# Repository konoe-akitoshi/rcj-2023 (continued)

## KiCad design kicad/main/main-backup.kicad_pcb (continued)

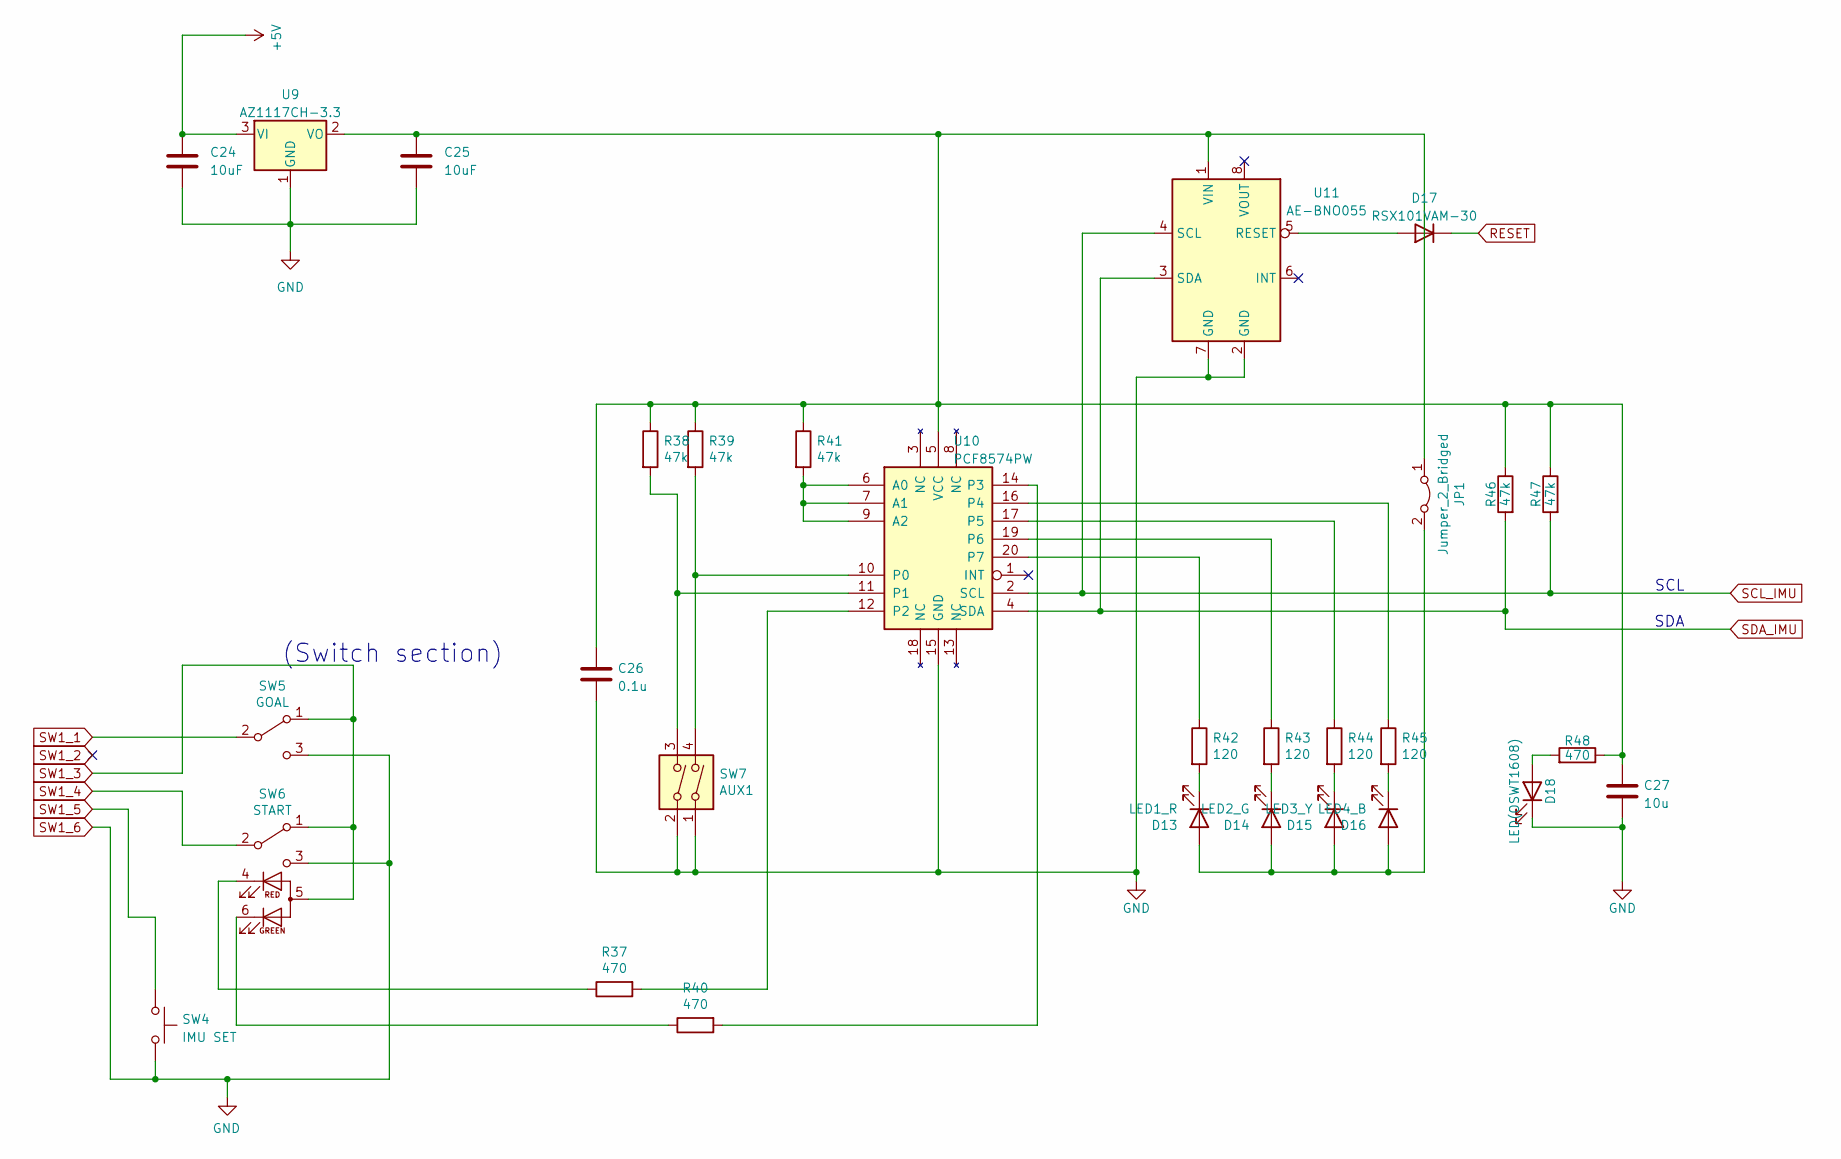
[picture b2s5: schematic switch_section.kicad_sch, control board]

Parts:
C24, C25: 10uF; C_0603_1608Metric_Pad1.08x0.95mm_HandSolder
C26: 0.1u; C_0603_1608Metric_Pad1.08x0.95mm_HandSolder
C27: 10u; C_0603_1608Metric_Pad1.08x0.95mm_HandSolder
D13: LED1_R; LED_SMLE13WBC8W1
D14: LED2_G; LED_SMLE13WBC8W1
D15: LED3_Y; LED_SMLE13WBC8W1
D16: LED4_B; LED_SMLE13WBC8W1
D17: RSX101VAM-30; D_0805_2012Metric_Pad1.15x1.40mm_HandSolder
D18: LED(OSWT1608); LED_SMLE13WBC8W1
JP1: Jumper_2_Bridged; PinHeader_1x02_P1.27mm_Vertical
R37, R40, R48: 470; R_0603_1608Metric_Pad0.98x0.95mm_HandSolder
R38, R39, R41, R46, R47: 47k; R_0603_1608Metric_Pad0.98x0.95mm_HandSolder
R42, R43, R44, R45: 120; R_0603_1608Metric_Pad0.98x0.95mm_HandSolder
SW4: IMU SET; SW_Tactile_Straight_KSA0Axx1LFTR
SW5: GOAL; MFS101D-14-Z
SW6: START; SW_NKK_B-12CCPRM
SW7: AUX1; SW_DIP_SPSTx02_Slide_9.78x7.26mm_W7.62mm_P2.54mm
U9: AZ1117CH-3.3; SOT-223-3_TabPin2
U10: PCF8574PW; TSSOP-20_4.4x6.5mm_P0.65mm
U11: AE-BNO055

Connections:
+5V: C24.1, U9.3 (VI); also elsewhere on the board
unnamed: C25.1, C26.1, C27.1, JP1.1 (A), R38.1, R39.1, R41.1, R46.1, R47.1, R48.1, U9.2 (VO), U10.5 (VCC), U11.1 (VIN)
unnamed: D13.1 (K), R42.2
unnamed: D13.2 (A), D14.2 (A), D15.2 (A), D16.2 (A), JP1.2 (B)
unnamed: D14.1 (K), R43.2
unnamed: D15.1 (K), R44.2
unnamed: D16.1 (K), R45.2
unnamed: D17.2 (A), U11.5 (RESET)
unnamed: D18.2 (A), R48.2
unnamed: R37.1, SW6.4 (KR)
unnamed: R37.2, U10.12 (P2)
unnamed: R38.2, SW7.3, U10.11 (P1)
unnamed: R39.2, SW7.4, U10.10 (P0)
unnamed: R40.1, SW6.6 (KG)
unnamed: R40.2, U10.14 (P3)
unnamed: R41.2, U10.6 (A0), U10.7 (A1), U10.9 (A2)
unnamed: R42.1, U10.20 (P7)
unnamed: R43.1, U10.19 (P6)
unnamed: R44.1, U10.17 (P5)
unnamed: R45.1, U10.16 (P4)
RESET: D17.1 (K); also elsewhere on the board
SCL_IMU: R47.2, U10.2 (SCL), U11.4 (SCL); also elsewhere on the board
SDA_IMU: R46.2, U10.4 (SDA), U11.3 (SDA); also elsewhere on the board
SW1_1: SW5.2 (B); also elsewhere on the board
SW1_3: SW5.1 (A), SW6.1 (A), SW6.5 (A); also elsewhere on the board
SW1_4: SW6.2 (B); also elsewhere on the board
SW1_5: SW4.1; also elsewhere on the board
SW1_6: C24.2, C25.2, C26.2, C27.2, D18.1 (K), SW4.2, SW5.3 (C), SW6.3 (C), SW7.1, SW7.2, U9.1 (GND), U10.15 (GND), U11.2 (GND), U11.7 (GND); also elsewhere on the board

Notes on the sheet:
SDA
SCL
(Switch section)

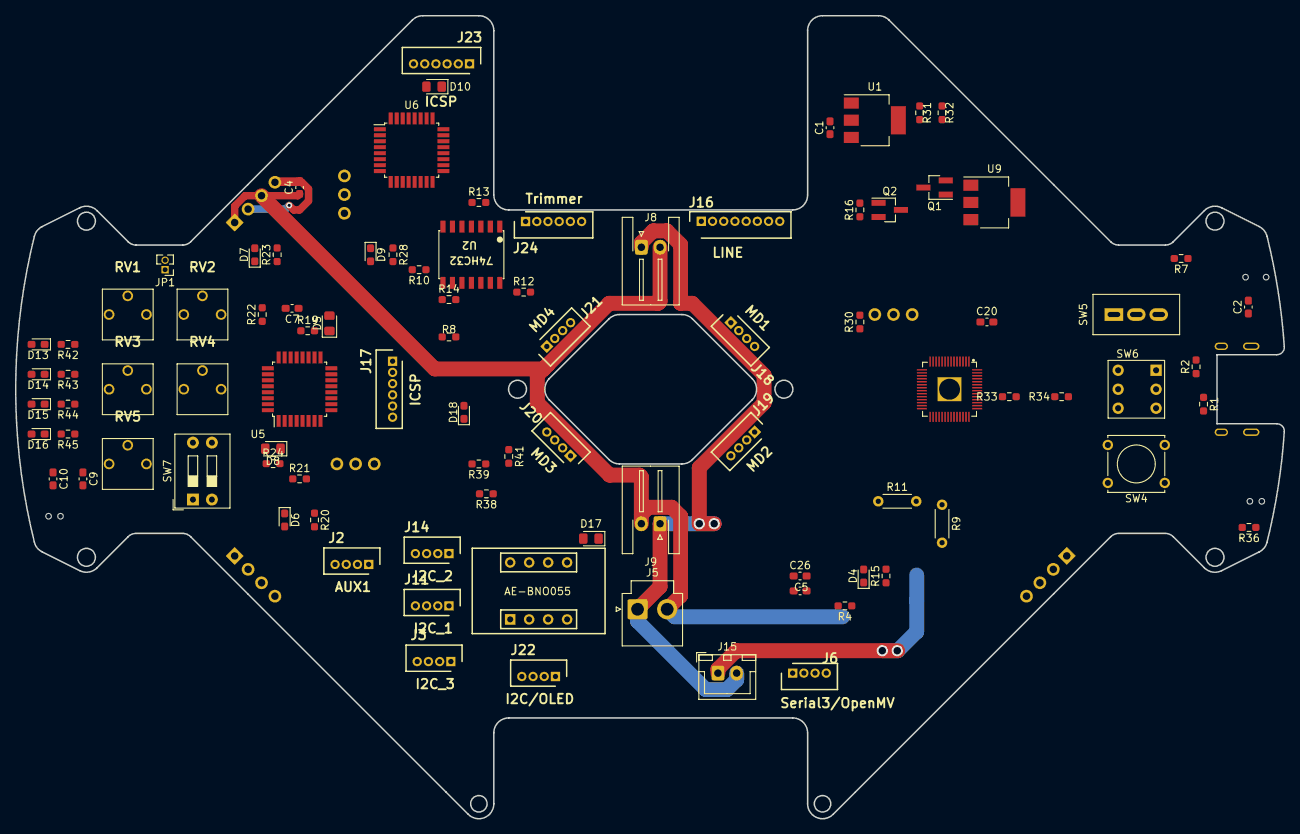
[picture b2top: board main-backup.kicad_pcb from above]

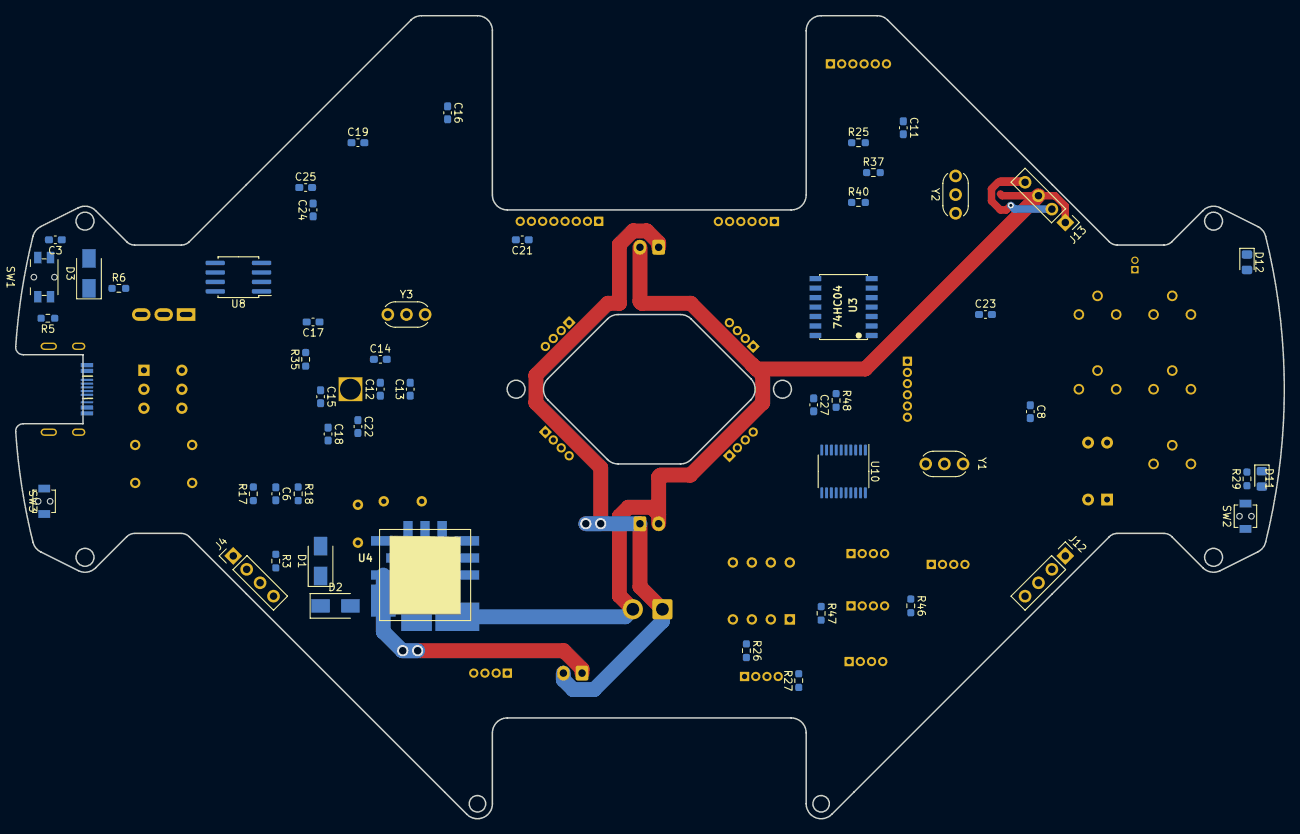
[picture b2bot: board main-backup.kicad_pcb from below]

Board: 2 copper layers, 169.8 x 107.5 mm, 144 parts (52 on the bottom side), 127 nets.
